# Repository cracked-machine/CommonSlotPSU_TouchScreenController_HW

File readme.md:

## TouchScreen Controller for 'CommonSlot' Server PSU

- Required Kicad Hardware library: https://github.com/cracked-machine/KicadLibrary
- Related SW Project: https://github.com/cracked-machine/CommonSlotPSU_TouchScreenController_SW

This project repurposes the power supply units (PSU) found in datacentre servers. The PSU are very powerful (12V @ 600W), efficient and compact.
They are useful for charging LIPO batteries (with some modification) and running brushless motors or any circuit that draws large amounts of current.
These PSU are replaced in industry on a regular basis - often well before their end-of-life - and can be found for a very reasonable price on the second hand market (ebay). This has been further aided by the rise (and decline) of the bitcoin "boom" a few years back.

The purpose of this project is to use a touch screen to control the server PSU. In turn the touchscreen will display information from the PSU including its status, voltage, current and other data via SMBUS protocol.

The touch screen is mounted on a PCB that connects to the server PSU via its "common slot" connector. This is a 64-pin card slot connector as shown below:

Information regarding specific PSU models can be hard to find. However, the design seems to be an unofficial standard across different manufacturers (HP, Murata, etc...). Some datasheets <sub>[[1]](#References)</sub>, application notes <sub>[[2]](#References)</sub> and schematics <sub>[[3]](#References)</sub> for similar models have been used to successfully glean relevant information. They will be referenced frequently throughout this page.

### System Overview

The controller board takes a 12VDC supply from the PSU (from the 12VSB card slot pin #37) and is booted as soon as the PSU is connected to the mains supply. This pin can supply 3A <sub>[[1]](#References)</sub> which is more than enough current to run the MCU and its LCD display.

A more detailed view of the interconnections between the high level system blocks are shown in the schematic page below.

### SMPS and PSU Output Enable block

The 12VSB rail is stepped down to 5V using a Texas Instruments [LMR14206 "Simple Switcher"](https://www.ti.com/lit/ds/symlink/lmr14206.pdf). This provides 0.6A at 84% efficiency with 0.5mV output ripple <sub>[[4]](#References)</sub>. For the higher current requirements of the OLED screen, a SMPS solution is preferable over the power disspiation that would be caused by a linear regulator (4.2W).

The 12VSB output is stepped down to 3V3 to supply the MCU. Since the MCU only draws 0.025A, the subsequent power disspation from the regulator - with copper pour heatsink - is acceptable (0.2W).

The PSU has insertion detection (using the PRESENT card slot pin #36). This alerts the PSU that it has been inserted into the back of a server housing. To enable this we simply connect this to 12VSB card slot pin #37 via a 22K resistor. With this in place we can enable the PSU output by pulling the PSON (card slot pin #33) to ground using an external NMOS. The gate of this NMOS is controlled by the MCU.

### Microcontroller block

The main requuirements for the MCU is SPI peripheral for the LCD display and I2C/SMBUS periperiphal for SMBUS communication. The STM32F072VB fullfills both these requirements and is also a small footprint (QFP64) and low cost (~£1).

SWD is used to provide in-circuit programming. The advanced speeds of JTAG are not required for this application.

### SMBUS Addressing

This is based on two schemes:

- HP 8bit addressing scheme using pins #27, #28 and #29. See [[3]](#References)
- Murata analog addressing scheme using resistance to ground. Pin #27 only. See [[2]](#References)

A single pole, double throw switch (SW2) is used to select the active address scheme.
A DIP switch (SW1) is used to select the bits of the address word in the HP scheme.
A DIP switch (SW3) is used to select the value of the address signal in the Murata scheme.

### Power Management block

When running a debug session (using SWD via the ICP interface) the NRST pin of the SWD cable is used to reset the MCU before downloading the binary file. However, this reset signal is not sufficient to fully reset the LCD Driver IC [TSC2046](https://www.ti.com/lit/ds/symlink/tsc2046.pdf). As such the LCD screen would only initialise when the entire system was power cycled, and would freeze during debug under reset.
After inspecting the signals on the LCD driver and the MCU it became apparent that a pulse extender was required to hold the TSC2046 in reset while the MCU re-initialized. The solution chosen was to use a timer IC [MIC1555](http://ww1.microchip.com/downloads/en/DeviceDoc/mic1555.pdf) to extend the pulse and a MOSFET driver IC to provide a current source for the LCD and driver.
The active low pulse was extended from 300ns <sub>[[5]](#References)</sub> to 1sec. Note, NRST is an active low signal and the MIC1555 timer outputs a positive-going signal. So the [MCP1415](http://ww1.microchip.com/downloads/en/DeviceDoc/20002092G.pdf) - which has an inverted output - was chosen.

The circuit design is shown below:

### References

1. [Datasheet: D1U86P-W-1600-12-HBxDC Series 86mm 1U Front End AC-DC Power Supply](RevB/docs/Murata_HP_datasheet_appnotes/d1u86p-w-1600-12-hbxdc.pdf)
2. [Application Note for D1U86P-12 Interface Connector Card](RevB/docs/Murata_HP_datasheet_appnotes/acan-50.pdf)
3. [HP_HSTNS-PL11_PS-2122-1C schematic](RevB/docs/Murata_HP_datasheet_appnotes/HP_HSTNS-PL11_PS-2122-1C.pdf)
4. [LMR14206 Webench design specs](RevB/docs/systemdesign/LMR14206_12V_to_5V_0.6A.csv)
5. [STM32F072VB Datasheet](https://www.st.com/resource/en/datasheet/stm32f072vb.pdf)

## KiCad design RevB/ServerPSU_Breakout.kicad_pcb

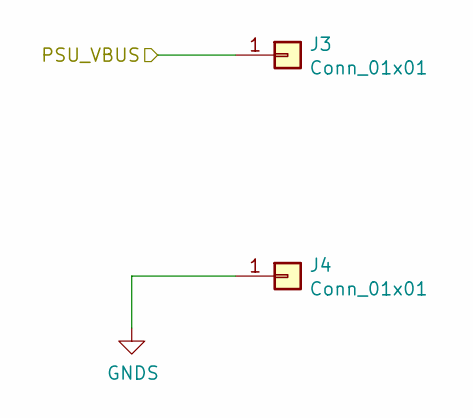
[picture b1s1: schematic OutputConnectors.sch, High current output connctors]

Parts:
J3, J4: Conn_01x01; MountingHole_6.4mm_M6_Pad_Via

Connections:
/OutputConnectors/PSU_VBUS: J3.1; also elsewhere on the board
GNDS: J4.1; also elsewhere on the board

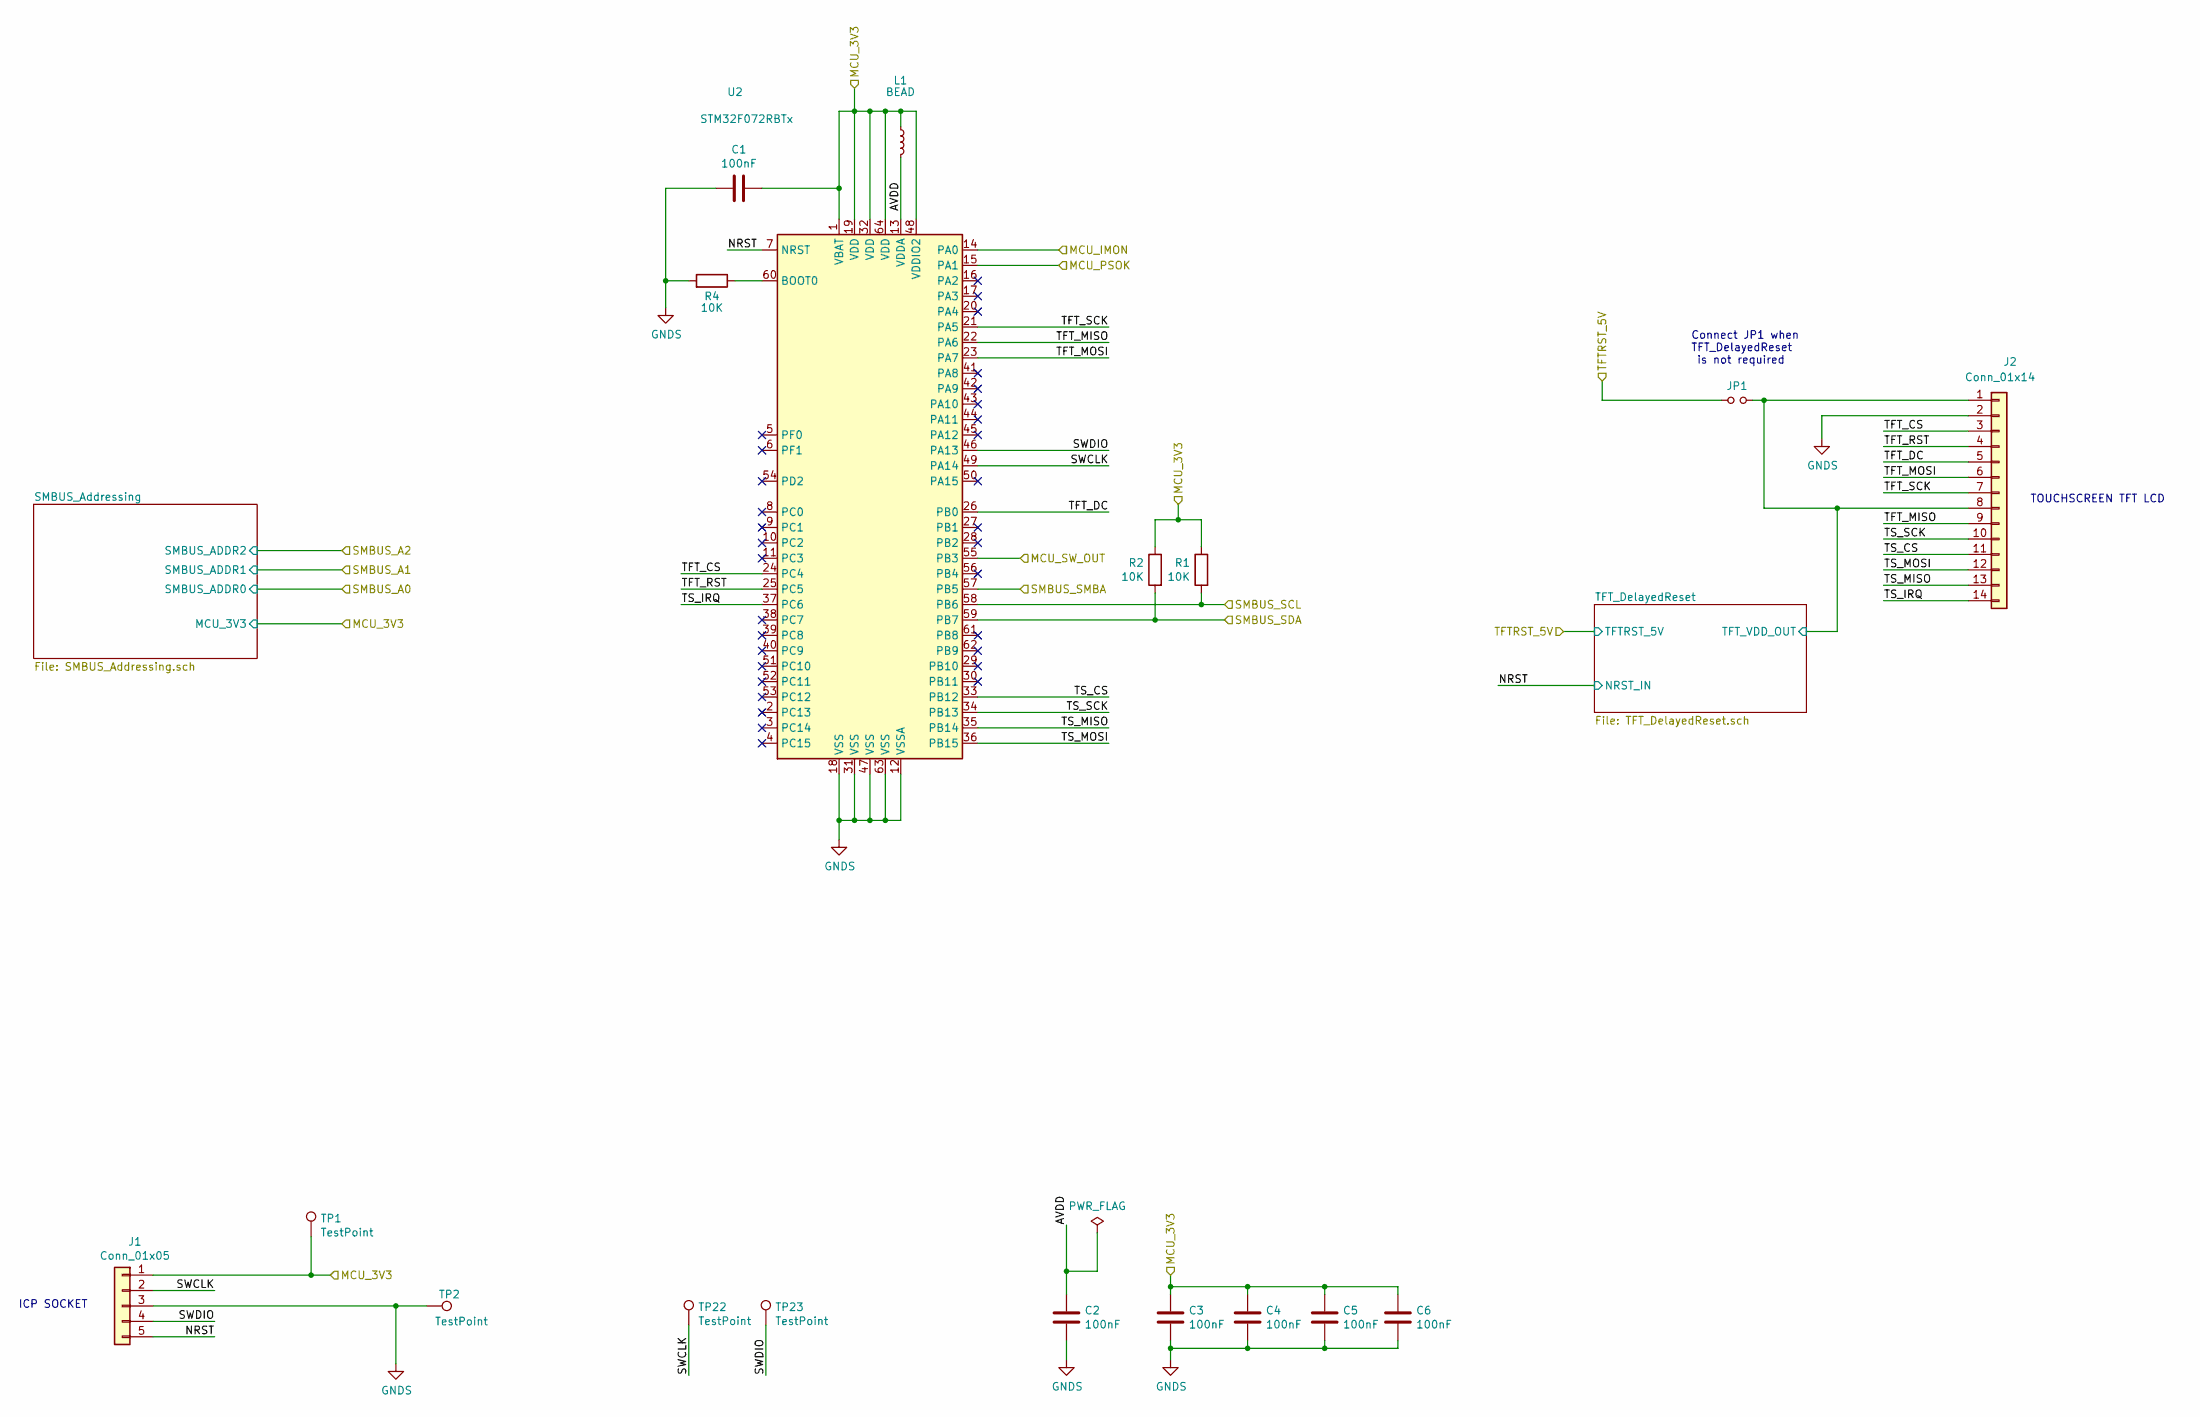
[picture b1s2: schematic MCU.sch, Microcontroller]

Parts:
C1, C2, C3, C4, C5, C6: 100nF; C_0805_2012Metric_Pad1.15x1.40mm_HandSolder
J1: Conn_01x05; PinHeader_1x05_P2.54mm_Horizontal
J2: Conn_01x14; ILI9341_ResitiveTouch_TFTLCD_2.8inch_85mm_50mm_FrontMount
JP1: Jumper_NO_Small; SolderJumper-2_P1.3mm_Open_Pad1.0x1.5mm
L1: BEAD; L_0805_2012Metric_Pad1.15x1.40mm_HandSolder
R1, R2, R4: 10K; R_0805_2012Metric_Pad1.15x1.40mm_HandSolder
TP1, TP2, TP22, TP23: TestPoint; TestPoint_Pad_1.0x1.0mm
U2: STM32F072RBTx; LQFP-64_10x10mm_P0.5mm

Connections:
/HighVoltageControl/MCU_3V3: C1.1, C3.2, C4.2, C5.2, C6.2, J1.1, L1.1, R1.1, R2.1, TP1.1, U2.1 (VBAT), U2.19 (VDD), U2.32 (VDD), U2.48 (VDDIO2), U2.64 (VDD); also elsewhere on the board
/HighVoltageControl/MCU_SW_IN: U2.55 (PB3); also elsewhere on the board
/MCU/AVDD: C2.2, L1.2, U2.13 (VDDA)
/MCU/MCU_IMON: U2.14 (PA0); also elsewhere on the board
/MCU/MCU_PSOK: U2.15 (PA1); also elsewhere on the board
/MCU/NRST: J1.5, U2.7 (NRST); also elsewhere on the board
/MCU/SWCLK: J1.2, TP22.1, U2.49 (PA14)
/MCU/SWDIO: J1.4, TP23.1, U2.46 (PA13)
/MCU/TFTRST_5V: JP1.1; also elsewhere on the board
/MCU/TFT_CS: J2.3, U2.24 (PC4)
/MCU/TFT_DC: J2.5, U2.26 (PB0)
/MCU/TFT_DelayedReset/TFT_VDD_OUT: J2.1, J2.8, JP1.2; also elsewhere on the board
/MCU/TFT_MISO: J2.9, U2.22 (PA6)
/MCU/TFT_MOSI: J2.6, U2.23 (PA7)
/MCU/TFT_RST: J2.4, U2.25 (PC5)
/MCU/TFT_SCK: J2.7, U2.21 (PA5)
/MCU/TS_CS: J2.11, U2.33 (PB12)
/MCU/TS_IRQ: J2.14, U2.37 (PC6)
/MCU/TS_MISO: J2.13, U2.35 (PB14)
/MCU/TS_MOSI: J2.12, U2.36 (PB15)
/MCU/TS_SCK: J2.10, U2.34 (PB13)
/PSUConnector/PSU_INT: U2.57 (PB5); also elsewhere on the board
/PSUConnector/PSU_SCL: R1.2, U2.58 (PB6); also elsewhere on the board
/PSUConnector/PSU_SDA: R2.2, U2.59 (PB7); also elsewhere on the board
GNDS: C1.2, C2.1, C3.1, C4.1, C5.1, C6.1, J1.3, J2.2, R4.2, TP2.1, U2.12 (VSSA), U2.18 (VSS), U2.31 (VSS), U2.47 (VSS), U2.63 (VSS); also elsewhere on the board
unnamed: R4.1, U2.60 (BOOT0)

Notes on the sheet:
TOUCHSCREEN TFT LCD
ICP SOCKET
Connect JP1 when TFT_DelayedReset is not required

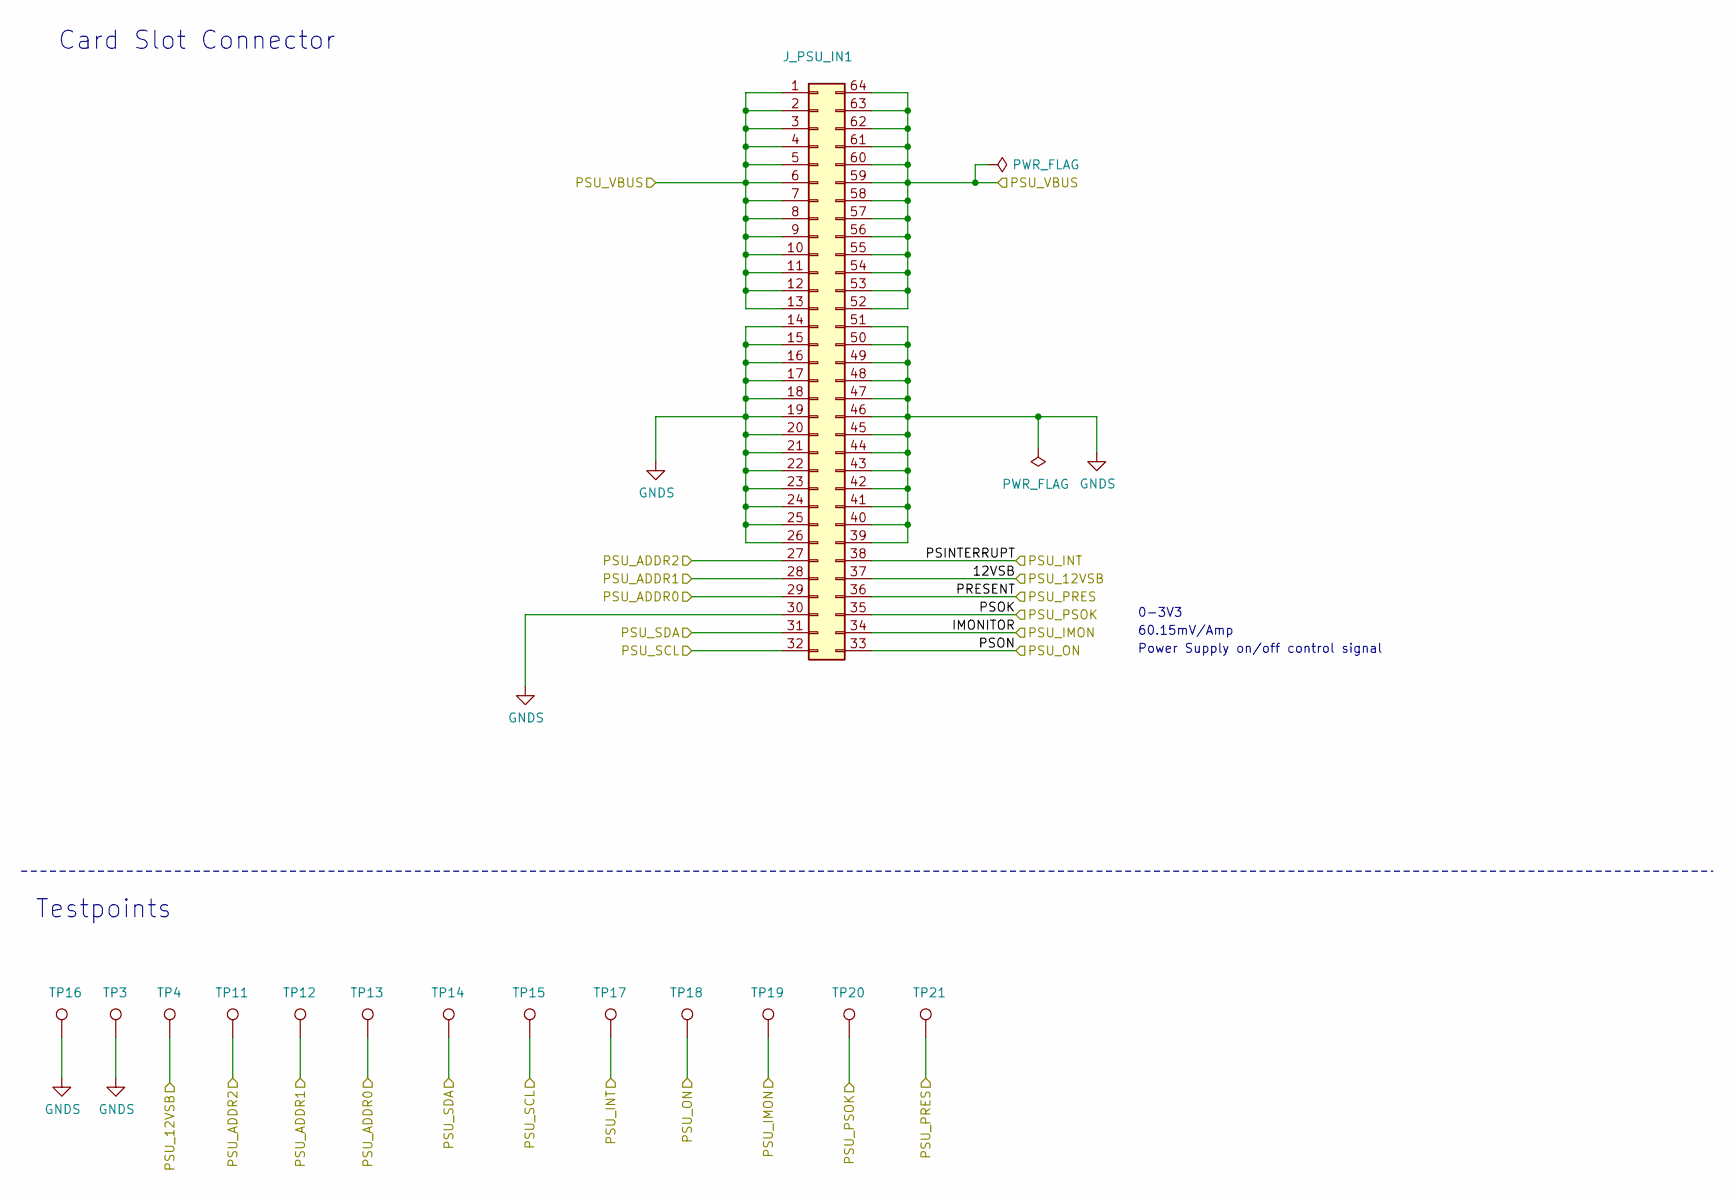
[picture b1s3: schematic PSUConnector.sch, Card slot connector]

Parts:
J_PSU_IN1: Amphenol FCI 10046971-001LF; Amphenol_FCI_10046971-001LF_2x32
TP3, TP4, TP11, TP12, TP13, TP14, TP15, TP16, TP17, TP18, TP19, TP20, TP21: TestPoint; TestPoint_Pad_1.0x1.0mm

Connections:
/HighVoltageControl/PSU_12VSB: J_PSU_IN1.37, TP4.1; also elsewhere on the board
/HighVoltageControl/PSU_ON: J_PSU_IN1.33, TP18.1; also elsewhere on the board
/HighVoltageControl/PSU_PRES: J_PSU_IN1.36, TP21.1; also elsewhere on the board
/MCU/MCU_IMON: J_PSU_IN1.34, TP19.1; also elsewhere on the board
/MCU/MCU_PSOK: J_PSU_IN1.35, TP20.1; also elsewhere on the board
/OutputConnectors/PSU_VBUS: J_PSU_IN1.1, J_PSU_IN1.2, J_PSU_IN1.3, J_PSU_IN1.4, J_PSU_IN1.5, J_PSU_IN1.6, J_PSU_IN1.7, J_PSU_IN1.8, J_PSU_IN1.9, J_PSU_IN1.10, J_PSU_IN1.11, J_PSU_IN1.12, J_PSU_IN1.13, J_PSU_IN1.52, J_PSU_IN1.53, J_PSU_IN1.54, J_PSU_IN1.55, J_PSU_IN1.56, J_PSU_IN1.57, J_PSU_IN1.58, J_PSU_IN1.59, J_PSU_IN1.60, J_PSU_IN1.61, J_PSU_IN1.62, J_PSU_IN1.63, J_PSU_IN1.64; also elsewhere on the board
/PSUConnector/PSU_ADDR0: J_PSU_IN1.29, TP13.1; also elsewhere on the board
/PSUConnector/PSU_ADDR1: J_PSU_IN1.28, TP12.1; also elsewhere on the board
/PSUConnector/PSU_ADDR2: J_PSU_IN1.27, TP11.1; also elsewhere on the board
/PSUConnector/PSU_INT: J_PSU_IN1.38, TP17.1; also elsewhere on the board
/PSUConnector/PSU_SCL: J_PSU_IN1.32, TP15.1; also elsewhere on the board
/PSUConnector/PSU_SDA: J_PSU_IN1.31, TP14.1; also elsewhere on the board
GNDS: J_PSU_IN1.14, J_PSU_IN1.15, J_PSU_IN1.16, J_PSU_IN1.17, J_PSU_IN1.18, J_PSU_IN1.19, J_PSU_IN1.20, J_PSU_IN1.21, J_PSU_IN1.22, J_PSU_IN1.23, J_PSU_IN1.24, J_PSU_IN1.25, J_PSU_IN1.26, J_PSU_IN1.30, J_PSU_IN1.39, J_PSU_IN1.40, J_PSU_IN1.41, J_PSU_IN1.42, J_PSU_IN1.43, J_PSU_IN1.44, J_PSU_IN1.45, J_PSU_IN1.46, J_PSU_IN1.47, J_PSU_IN1.48, J_PSU_IN1.49, J_PSU_IN1.50, J_PSU_IN1.51, TP3.1, TP16.1; also elsewhere on the board

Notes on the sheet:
0-3V3
Power Supply on/off control signal
60.15mV/Amp
Testpoints
Card Slot Connector

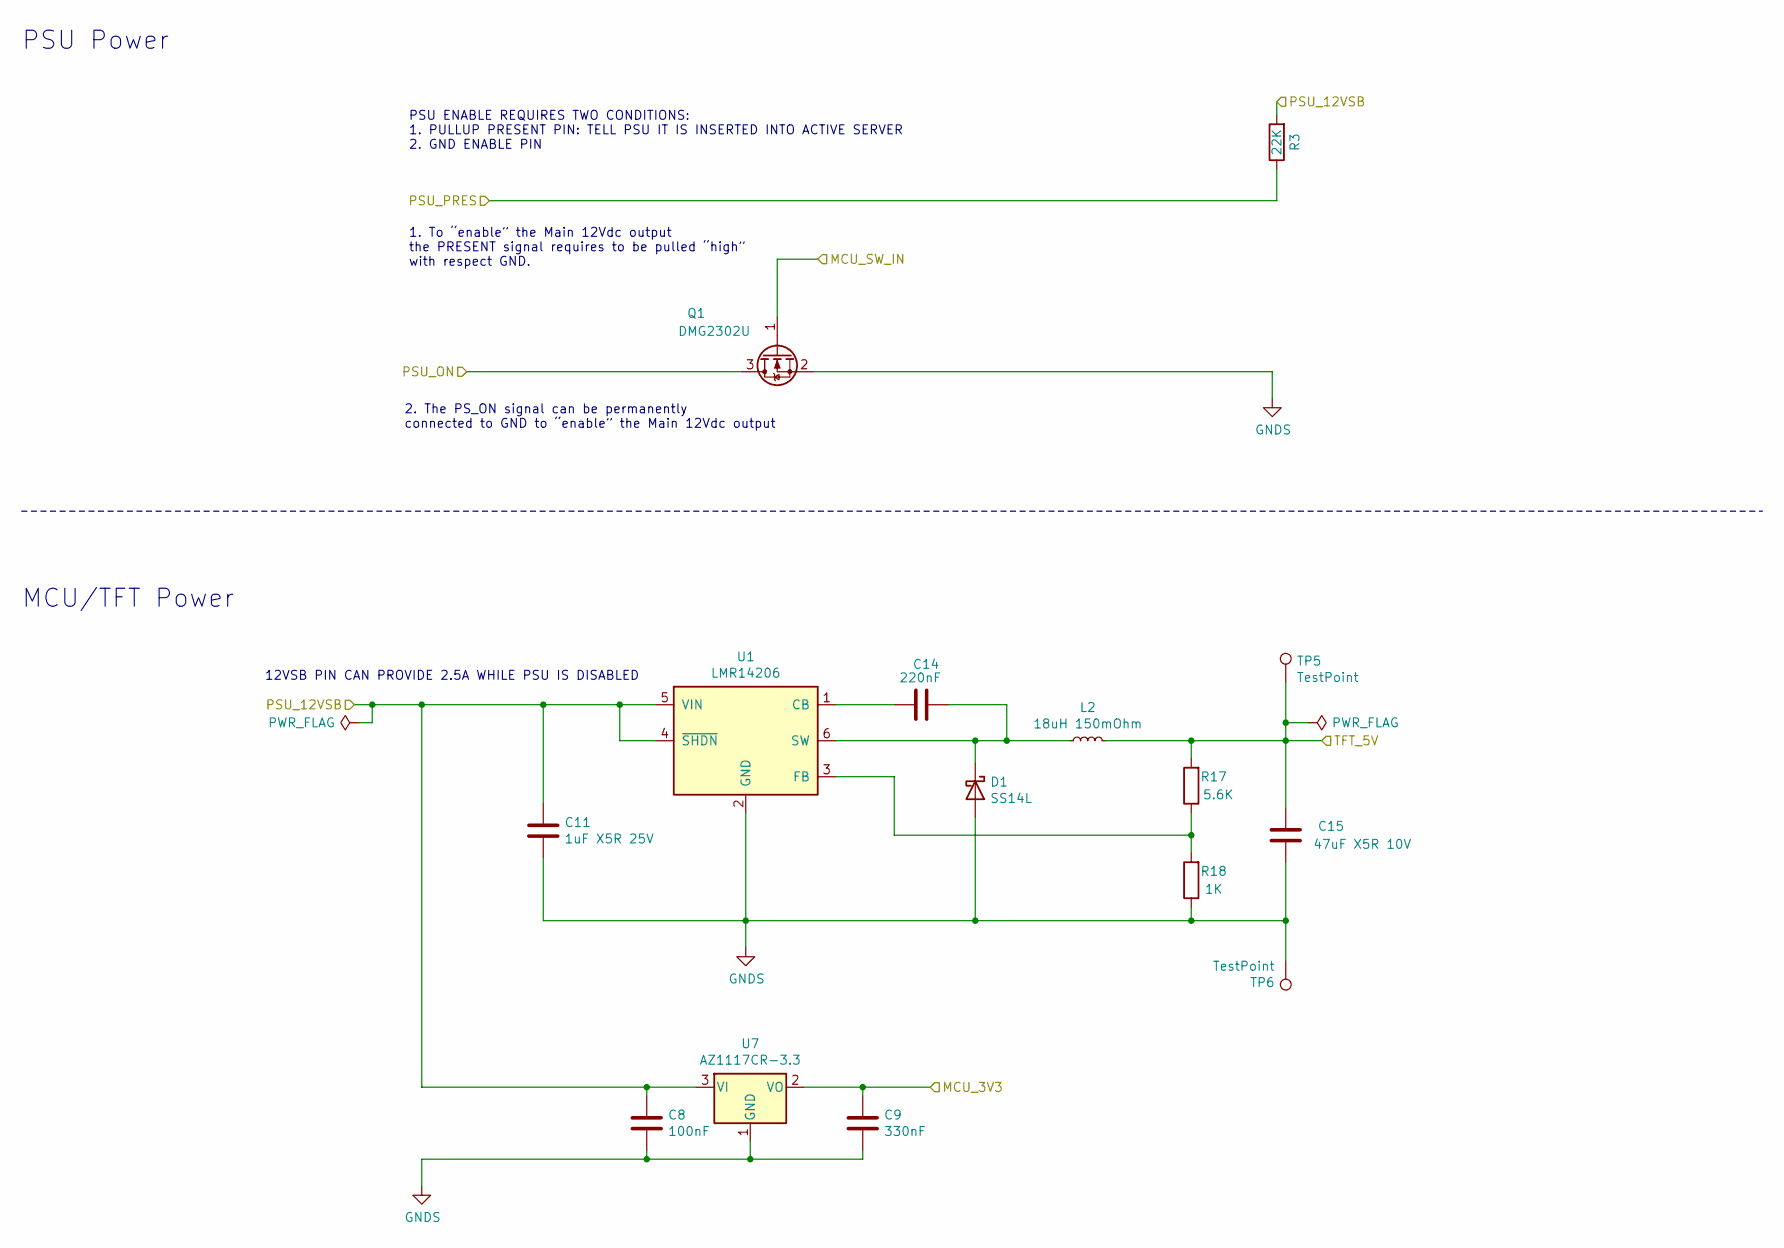
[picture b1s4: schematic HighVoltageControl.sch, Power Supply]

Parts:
C8: 100nF; C_0805_2012Metric_Pad1.15x1.40mm_HandSolder
C9: 330nF; C_0805_2012Metric_Pad1.15x1.40mm_HandSolder
C11: 1uF X5R 25V; C_0805_2012Metric_Pad1.15x1.40mm_HandSolder
C14: 220nF; C_0805_2012Metric_Pad1.15x1.40mm_HandSolder
C15: 47uF X5R 10V; C_0805_2012Metric_Pad1.15x1.40mm_HandSolder
D1: SS14L; D_SOD-123F
L2: 18uH 150mOhm; L_Bourns-SRN8040_8x8.15mm
Q1: DMG2302U; SOT-23
R3: 22K; R_0805_2012Metric_Pad1.15x1.40mm_HandSolder
R17: 5.6K; R_0805_2012Metric_Pad1.15x1.40mm_HandSolder
R18: 1K; R_0805_2012Metric_Pad1.15x1.40mm_HandSolder
TP5, TP6: TestPoint; TestPoint_Pad_1.0x1.0mm
U1: LMR14206; SOT-23-6
U7: AZ1117CR-3.3; SOT-89-3_Handsoldering

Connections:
/HighVoltageControl/MCU_3V3: C9.1, U7.2 (VO); also elsewhere on the board
/HighVoltageControl/MCU_SW_IN: Q1.1 (G); also elsewhere on the board
/HighVoltageControl/PSU_12VSB: C8.1, C11.1, R3.2, U1.4 (~SHDN), U1.5 (VIN), U7.3 (VI); also elsewhere on the board
/HighVoltageControl/PSU_ON: Q1.3 (D); also elsewhere on the board
/HighVoltageControl/PSU_PRES: R3.1; also elsewhere on the board
/MCU/TFTRST_5V: C15.2, L2.2, R17.2, TP5.1; also elsewhere on the board
GNDS: C8.2, C9.2, C11.2, C15.1, D1.2 (A), Q1.2 (S), R18.1, TP6.1, U1.2 (GND), U7.1 (GND); also elsewhere on the board
unnamed: C14.1, D1.1 (K), L2.1, U1.6 (SW)
unnamed: C14.2, U1.1 (CB)
unnamed: R17.1, R18.2, U1.3 (FB)

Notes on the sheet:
1. To “enable” the Main 12Vdc output the PRESENT signal requires to be pulled “high” with respect GND.
2. The PS_ON signal can be permanently connected to GND to “enable” the Main 12Vdc output
PSU ENABLE REQUIRES TWO CONDITIONS: 1. PULLUP PRESENT PIN: TELL PSU IT IS INSERTED INTO ACTIVE SERVER 2. GND ENABLE PIN
12VSB PIN CAN PROVIDE 2.5A WHILE PSU IS DISABLED
PSU Power
MCU/TFT Power

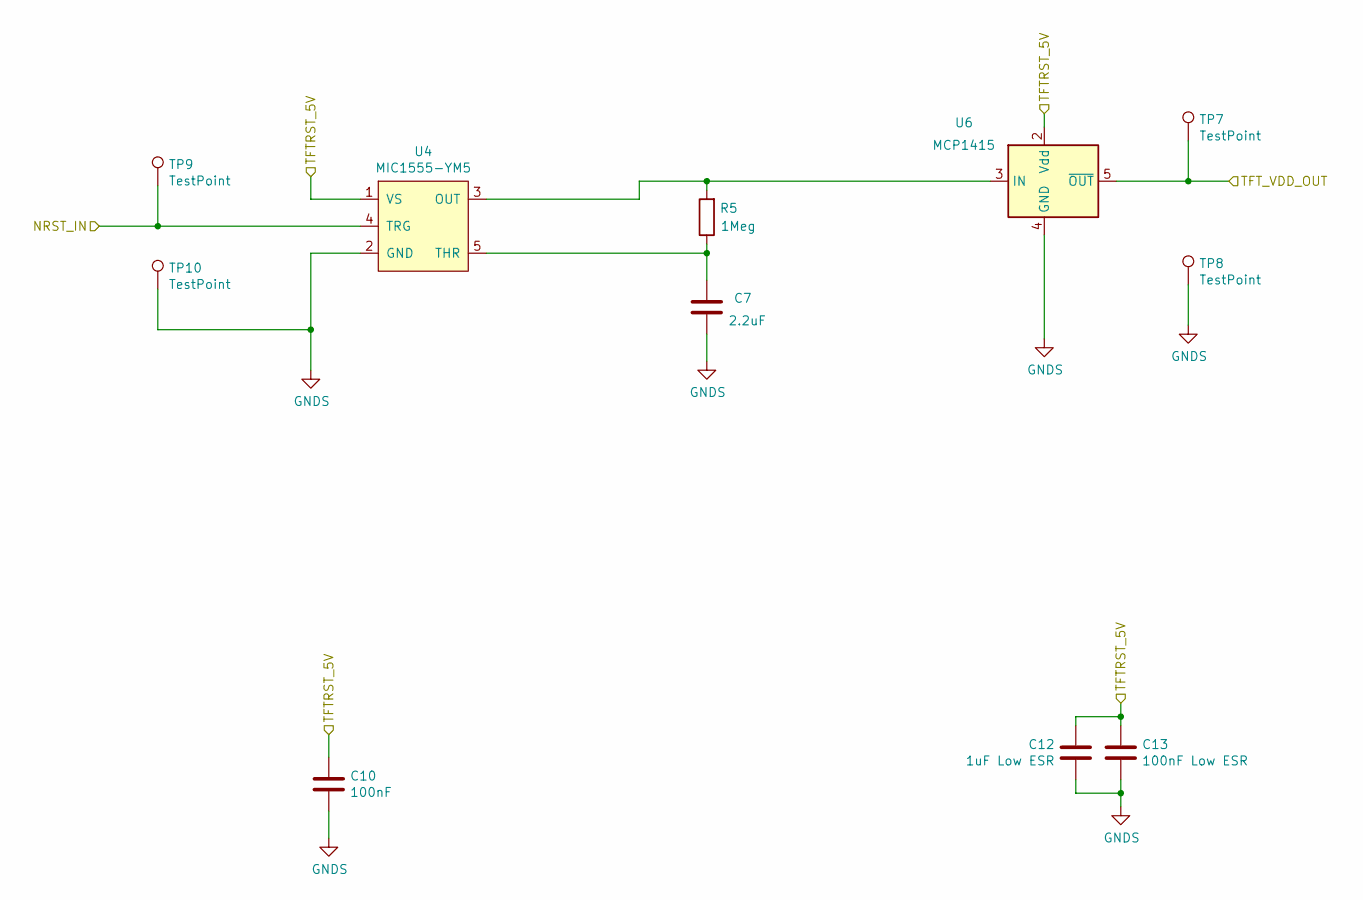
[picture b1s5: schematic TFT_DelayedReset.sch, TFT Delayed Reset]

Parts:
C7: 2.2uF; C_0805_2012Metric_Pad1.15x1.40mm_HandSolder
C10: 100nF; C_0805_2012Metric_Pad1.15x1.40mm_HandSolder
C12: 1uF Low ESR; C_0805_2012Metric_Pad1.15x1.40mm_HandSolder
C13: 100nF Low ESR; C_0805_2012Metric_Pad1.15x1.40mm_HandSolder
R5: 1Meg; R_0805_2012Metric_Pad1.15x1.40mm_HandSolder
TP7, TP8, TP9, TP10: TestPoint; TestPoint_Pad_1.0x1.0mm
U4: MIC1555-YM5; SOT-23-5_HandSoldering
U6: MCP1415; SOT-23-5

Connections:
/MCU/NRST: TP9.1, U4.4 (TRG); also elsewhere on the board
/MCU/TFTRST_5V: C10.1, C12.2, C13.1, U4.1 (VS), U6.2 (Vdd); also elsewhere on the board
/MCU/TFT_DelayedReset/TFT_VDD_OUT: TP7.1, U6.5 (~OUT); also elsewhere on the board
GNDS: C7.1, C10.2, C12.1, C13.2, TP8.1, TP10.1, U4.2 (GND), U6.4 (GND); also elsewhere on the board
unnamed: C7.2, R5.1, U4.5 (THR)
unnamed: R5.2, U4.3 (OUT), U6.3 (IN)

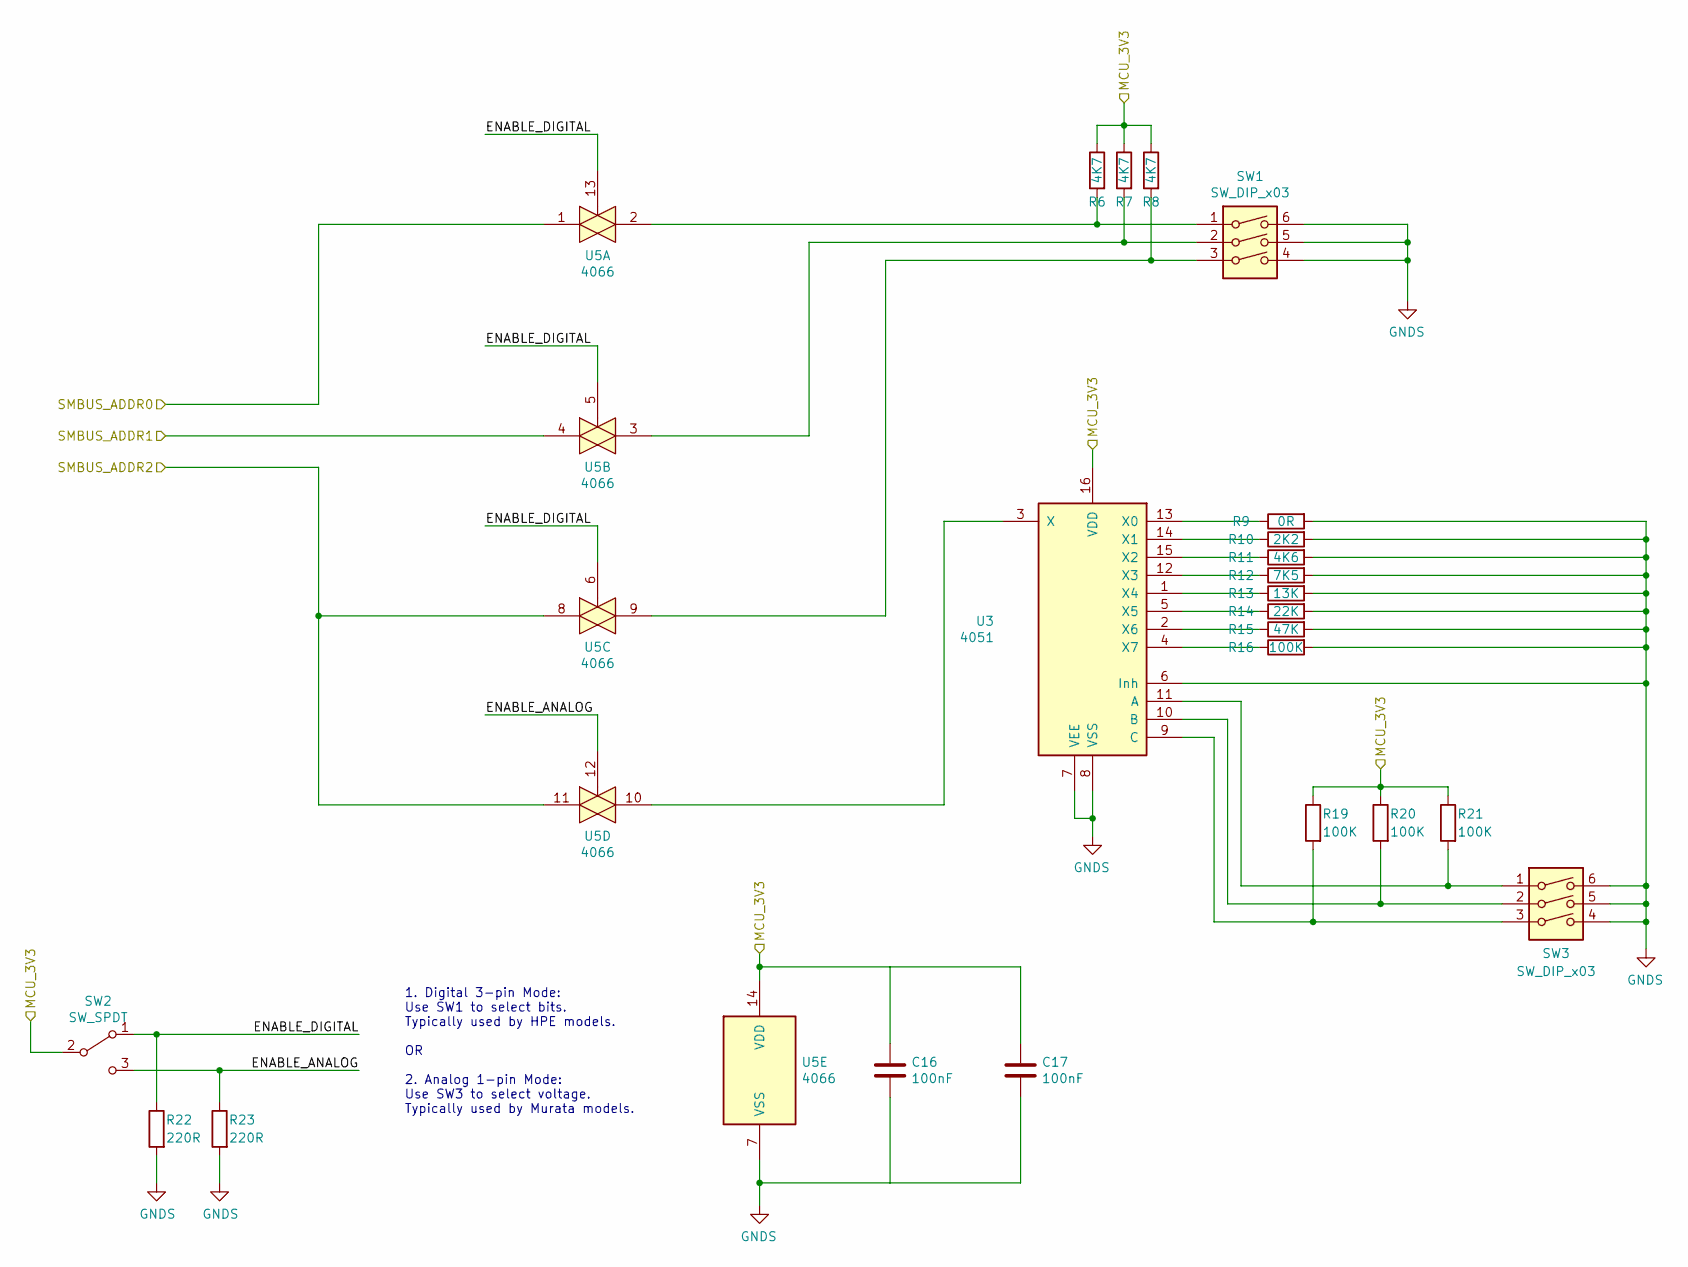
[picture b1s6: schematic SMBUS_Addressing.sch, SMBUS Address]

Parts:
C16, C17: 100nF; C_0805_2012Metric_Pad1.15x1.40mm_HandSolder
R6, R7, R8: 4K7; R_0805_2012Metric_Pad1.15x1.40mm_HandSolder
R9: 0R; R_0805_2012Metric_Pad1.15x1.40mm_HandSolder
R10: 2K2; R_0805_2012Metric_Pad1.15x1.40mm_HandSolder
R11: 4K6; R_0805_2012Metric_Pad1.15x1.40mm_HandSolder
R12: 7K5; R_0805_2012Metric_Pad1.15x1.40mm_HandSolder
R13: 13K; R_0805_2012Metric_Pad1.15x1.40mm_HandSolder
R14: 22K; R_0805_2012Metric_Pad1.15x1.40mm_HandSolder
R15: 47K; R_0805_2012Metric_Pad1.15x1.40mm_HandSolder
R16, R19, R20, R21: 100K; R_0805_2012Metric_Pad1.15x1.40mm_HandSolder
R22, R23: 220R; R_0805_2012Metric_Pad1.15x1.40mm_HandSolder
SW1, SW3: SW_DIP_x03; SW_DIP_SPSTx03_Slide_6.7x9.18mm_W8.61mm_P2.54mm_LowProfile
SW2: SW_SPDT; PinHeader_1x03_P2.54mm_Vertical
U3: 4051; SOIC-16_3.9x9.9mm_P1.27mm
U5: 4066; SOIC-14_3.9x8.7mm_P1.27mm

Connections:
/HighVoltageControl/MCU_3V3: C16.1, C17.1, R6.1, R7.1, R8.1, R19.1, R20.1, R21.1, SW2.2 (B), U3.16 (VDD), U5.14 (VDD); also elsewhere on the board
/MCU/SMBUS_Addressing/ENABLE_ANALOG: R23.1, SW2.3 (C), U5.12
/MCU/SMBUS_Addressing/ENABLE_DIGITAL: R22.1, SW2.1 (A), U5.5, U5.6, U5.13
/PSUConnector/PSU_ADDR0: U5.1; also elsewhere on the board
/PSUConnector/PSU_ADDR1: U5.4; also elsewhere on the board
/PSUConnector/PSU_ADDR2: U5.8, U5.11; also elsewhere on the board
GNDS: C16.2, C17.2, R9.2, R10.2, R11.2, R12.2, R13.2, R14.2, R15.2, R16.2, R22.2, R23.2, SW1.4, SW1.5, SW1.6, SW3.4, SW3.5, SW3.6, U3.6 (Inh), U3.7 (VEE), U3.8 (VSS), U5.7 (VSS); also elsewhere on the board
unnamed: R6.2, SW1.1, U5.2
unnamed: R7.2, SW1.2, U5.3
unnamed: R8.2, SW1.3, U5.9
unnamed: R9.1, U3.13 (X0)
unnamed: R10.1, U3.14 (X1)
unnamed: R11.1, U3.15 (X2)
unnamed: R12.1, U3.12 (X3)
unnamed: R13.1, U3.1 (X4)
unnamed: R14.1, U3.5 (X5)
unnamed: R15.1, U3.2 (X6)
unnamed: R16.1, U3.4 (X7)
unnamed: R19.2, SW3.3, U3.9 (C)
unnamed: R20.2, SW3.2, U3.10 (B)
unnamed: R21.2, SW3.1, U3.11 (A)
unnamed: U3.3 (X), U5.10

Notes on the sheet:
1. Digital 3-pin Mode: Use SW1 to select bits. Typically used by HPE models. OR 2. Analog 1-pin Mode: Use SW3 to select voltage. Typically used by Murata models.

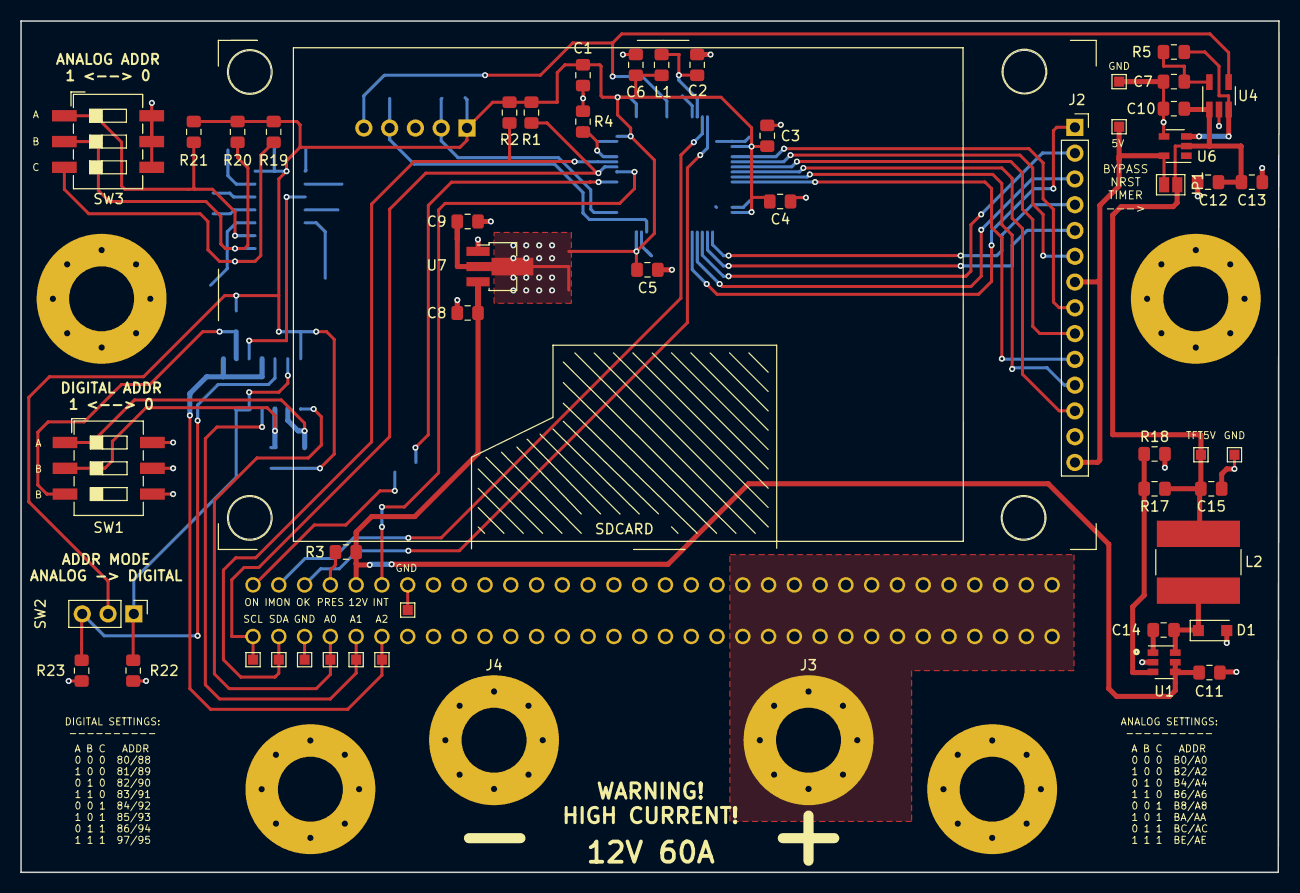
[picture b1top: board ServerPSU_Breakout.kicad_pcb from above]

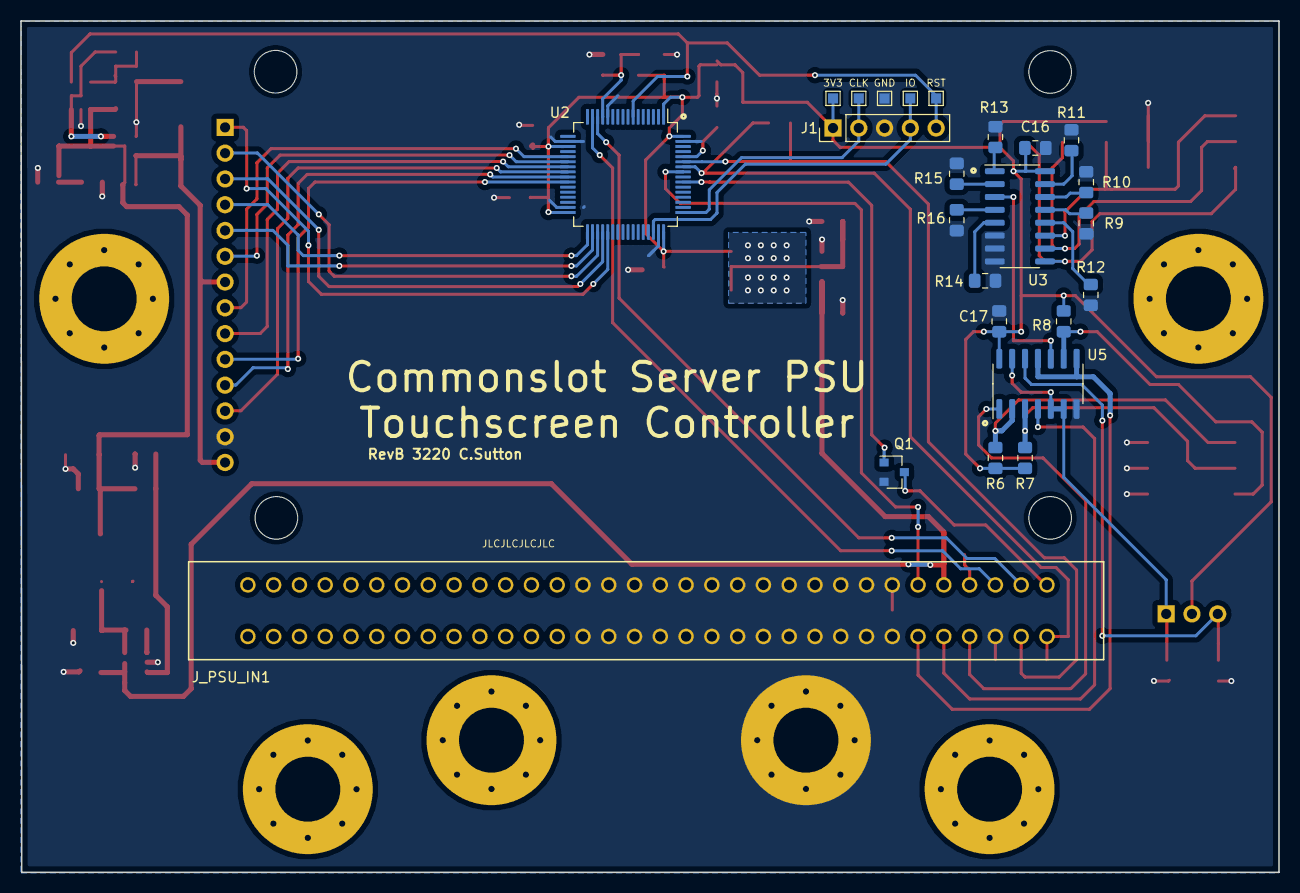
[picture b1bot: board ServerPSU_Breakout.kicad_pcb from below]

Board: 2 copper layers, 124.0 x 83.9 mm, 76 parts (24 on the bottom side), 55 nets.

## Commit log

2019-02-21 updated schematic
    Switched single point outputs to 6 pin outputs
2019-02-22 Created Layout
2019-03-06 RevB update
2020-01-13 updated design
    - corrected control pins
2020-06-30 Added New RevC design
2020-07-01 UPDATED SWITCH WIRING
2020-07-02 replaced stm32F051 with stm32F072
2020-07-04 layout draft
2020-07-05 moved SPI2 traces on MCU
2020-07-16 Added TFT Delayed Reset sub circuit
    changed NCS1S1203SC to NCS1S1205SC
2020-07-16 Swapped LM555 with MIC1555
2020-07-19 updated hw
    - added SMBUS address HW
    - Changed Isolated DC Module to TI SimpleSwitcher IC
2020-07-19 Completed RevA
2020-07-19 save
2020-07-19 Corrected Pin numbering errors :)
2020-07-19 regen schema docs
2020-07-25 backup
2020-07-26 updates
    set U3 4051 address resistors to E12 values
2020-07-26 Separated out RevA and RevB
    - Tidied up RevA schematic
    - Made changes to RevB layout
2020-07-26 update RevB design
    - Corrected PSU_ON n-chan. Drain and Source swapped.
2020-07-26 updated revb
    added missing pullup resistors
2020-08-06 hw update
    - Reduced RevB layout dimensions
2020-08-07 hw update
    - changed third dip switch to cd4066 and spdt slide switch
2020-08-07 docs update
2020-08-08 hw update
    updated revb. Added board connectors for device stacking
2020-08-09 hw update
    revb layout completed
2020-09-09 added readme
2020-09-11 added timing diagram to readme
2020-10-26 Add .circleci/config.yml
